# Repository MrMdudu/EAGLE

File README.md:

# EAGLE

Eagle files of a SSTC (Solid state tesla coil) project

Schematic from http://www.loneoceans.com/labs/sstc2/
Where you can learn a lot about Tesla coils

Board layout made by myself and not yet tested.

Edit: PCBs were assembled and they work as intended :)

This is my first try at PCD design and there are certainly a lot of flaws

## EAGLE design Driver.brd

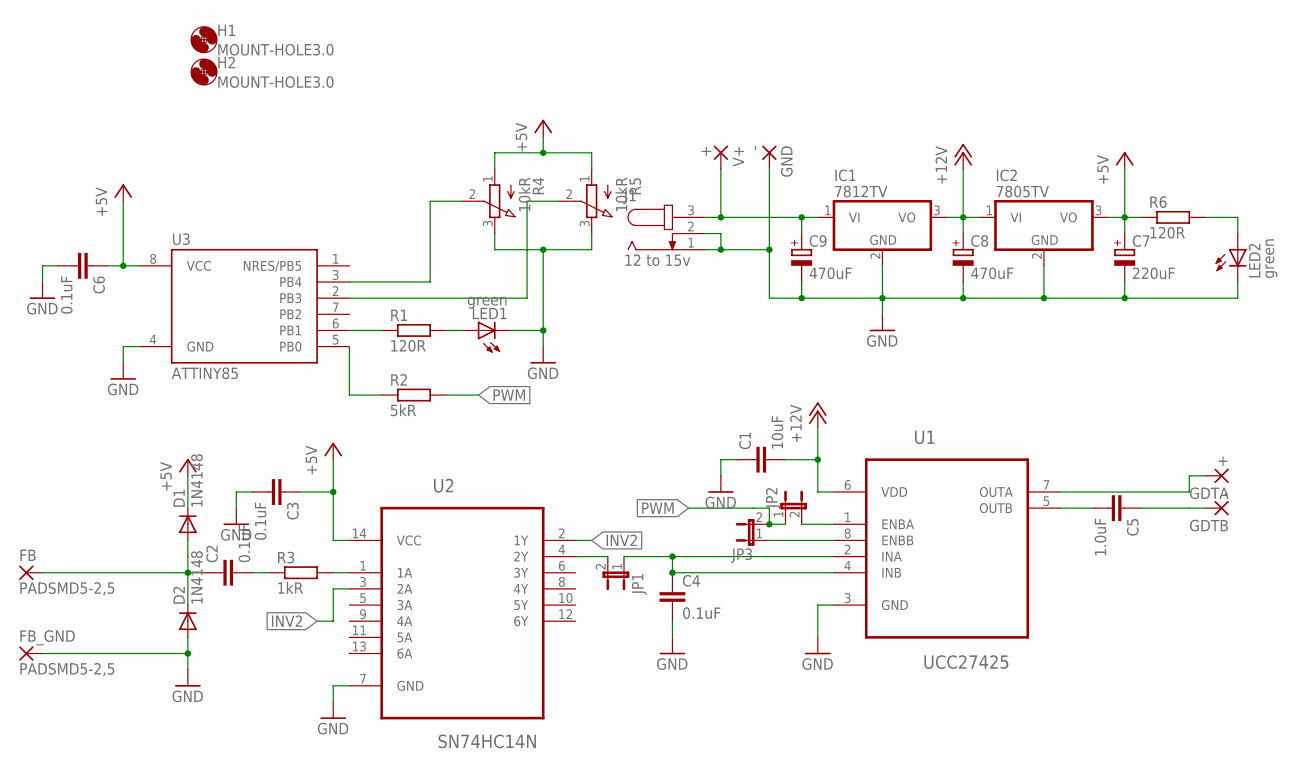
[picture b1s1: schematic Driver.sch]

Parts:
C1: 10uF; 1210
C2, C3, C4, C6: 0.1uF; C0805
C5: 1.0uF; 0805
C7: 220uF; E3,5-8
C8, C9: 470uF; E3,5-10
D1, D2: 1N4148; DO35-7
FB: PADSMD5-2,5; 5-2,5
FB_GND: PADSMD5-2,5; 5-2,5
GDTA: +; 4,16O1,6
GDTB: -; 4,16O1,6
GND: -; 4,16O1,6
H1, H2: MOUNT-HOLE3.0; 3,0
IC1: 7812TV; TO220V
IC2: 7805TV; TO220V
J1: 12 to 15v; SPC4078
JP1, JP2, JP3: JP1E; JP1
LED1, LED2: green; CHIPLED_0805
R1, R6: 120R; R0805
R2: 5kR; R0805
R3: 1kR; R0805
R4, R5: 10kR; 3RP/1610N
U1: UCC27425; DIP254P762X419-8
U2: SN74HC14N; DIP254P762X508-14
U3: ATTINY85; DIL08
V+: +; 4,16O1,6

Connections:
+5V: C3.1, C6.1, C7.+, D1.C, IC2.3 (VO), R4.1 (A), R5.1 (A), R6.1, U2.14 (VCC), U3.8 (VCC)
+12V: C1.2, C8.+, IC1.3 (VO), IC2.1 (VI), U1.6 (VDD)
GDTA: GDTA.1, U1.7 (OUTA)
GDTB: C5.1, GDTB.1
GND: C1.1, C3.2, C4.2, C6.2, C7.-, C8.-, C9.-, D2.A, FB_GND.1, GND.1, IC1.2 (GND), IC2.2 (GND), J1.1, J1.2, LED1.C, LED2.C, R4.3 (E), R5.3 (E), U1.3 (GND), U2.7 (GND), U3.4 (GND)
INV2: U2.2 (1Y), U2.3 (2A)
unnamed: R3.2, U2.1 (1A)
unnamed: C2.2, R3.1
unnamed: C2.1, D1.A, D2.C, FB.1
unnamed: C4.1, JP1.1, U1.2 (INA), U1.4 (INB)
unnamed: R1.1, U3.6 (PB1)
unnamed: LED1.A, R1.2
unnamed: C5.2, U1.5 (OUTB)
unnamed: R4.2 (S), U3.3 (PB4)
unnamed: R5.2 (S), U3.2 (PB3)
unnamed: R2.1, U3.5 (PB0)
unnamed: LED2.A, R6.2
unnamed: JP2.2, U1.1 (ENBA)
unnamed: C9.+, IC1.1 (VI), J1.3, V+.1
unnamed: JP1.2, U2.4 (2Y)
unnamed: JP3.1, U1.8 (ENBB)
PWM: JP2.1, JP3.2, R2.2

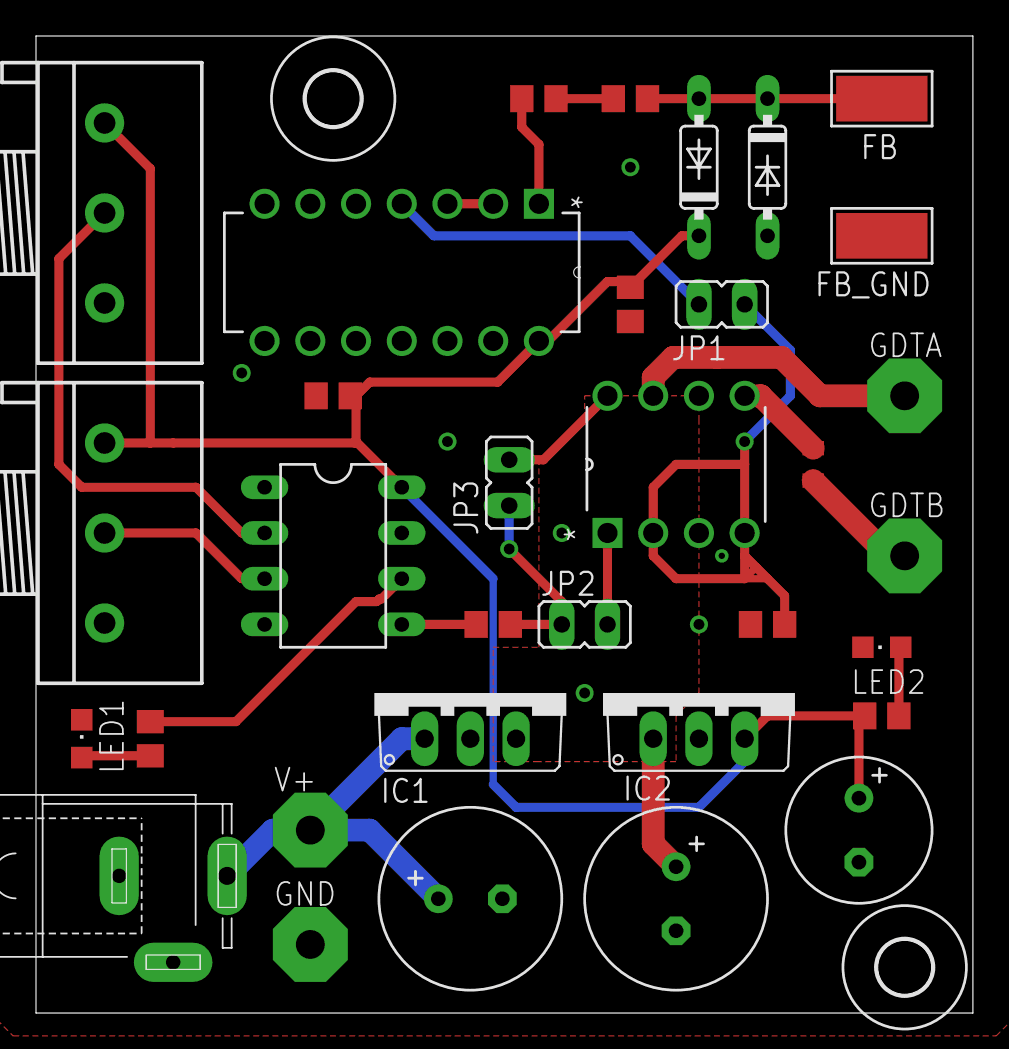
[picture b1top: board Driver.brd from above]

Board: 2 copper layers, 52.0 x 54.3 mm, 36 parts (1 on the bottom side), 22 nets.

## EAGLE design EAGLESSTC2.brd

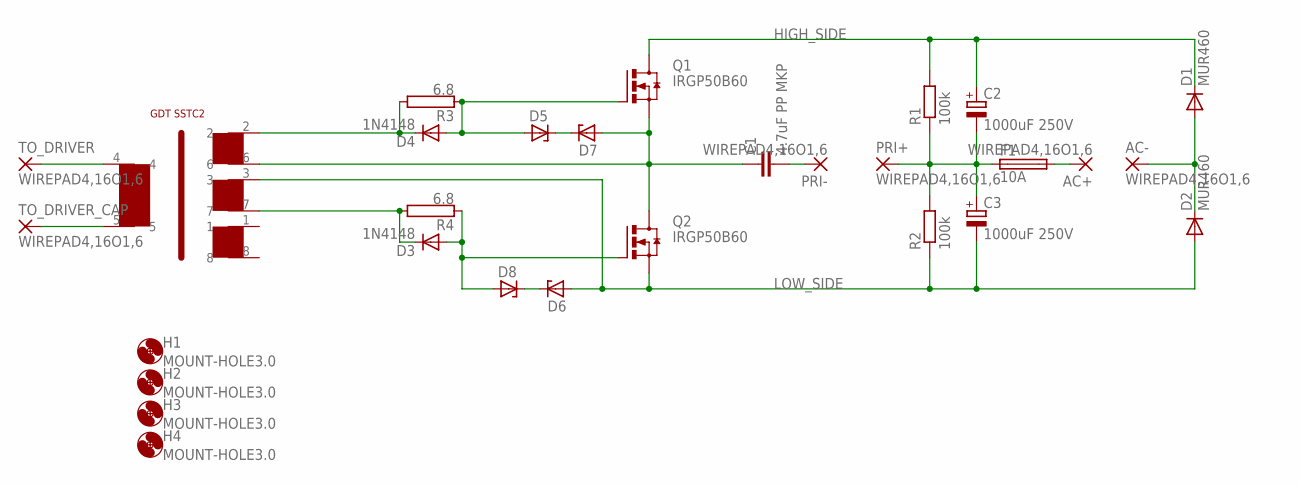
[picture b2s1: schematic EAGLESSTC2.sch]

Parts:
AC+: WIREPAD4,16O1,6; 4,16O1,6
AC-: WIREPAD4,16O1,6; 4,16O1,6
C1: 4.7uF PP MKP; C37.5B20
C2, C3: 1000uF 250V; EB35D
D1, D2: MUR460; C2673
D3, D4: 1N4148; DO35-10
D5, D6, D7, D8: ZENER-DIODEZD-10; ZDIO-10
F1: 10A; SH22
H1, H2, H3, H4: MOUNT-HOLE3.0; 3,0
PRI+: WIREPAD4,16O1,6; 4,16O1,6
PRI-: WIREPAD4,16O1,6; 4,16O1,6
Q1, Q2: IRGP50B60; TO-247AD-V
R1, R2: 100k; 0207/10
R3, R4: 6.8; RWM6X22
TO_DRIVER: WIREPAD4,16O1,6; 4,16O1,6
TO_DRIVER_CAP: WIREPAD4,16O1,6; 4,16O1,6
U$1: ATX-TRANSFORMER_01

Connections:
CAP_TO_GDT: TO_DRIVER_CAP.1, U$1.5
DRIVER_PIN7: TO_DRIVER.1, U$1.4
HIGH_SIDE: C2.+, D1.C, Q1.D, R1.2
LOW_SIDE: C3.-, D2.A, D6.A, Q2.S, R2.1, U$1.3
unnamed: C1.1, D7.A, Q1.S, Q2.D, U$1.6
unnamed: C1.2, PRI-.1
unnamed: AC+.1, F1.2
unnamed: D6.C, D8.C
unnamed: D5.C, D7.C
unnamed: AC-.1, D1.A, D2.C
unnamed: D3.C, R4.2, U$1.7
unnamed: C2.-, C3.+, F1.1, PRI+.1, R1.1, R2.2
unnamed: D4.C, R3.2, U$1.2
unnamed: D4.A, D5.A, Q1.G, R3.1
unnamed: D3.A, D8.A, Q2.G, R4.1

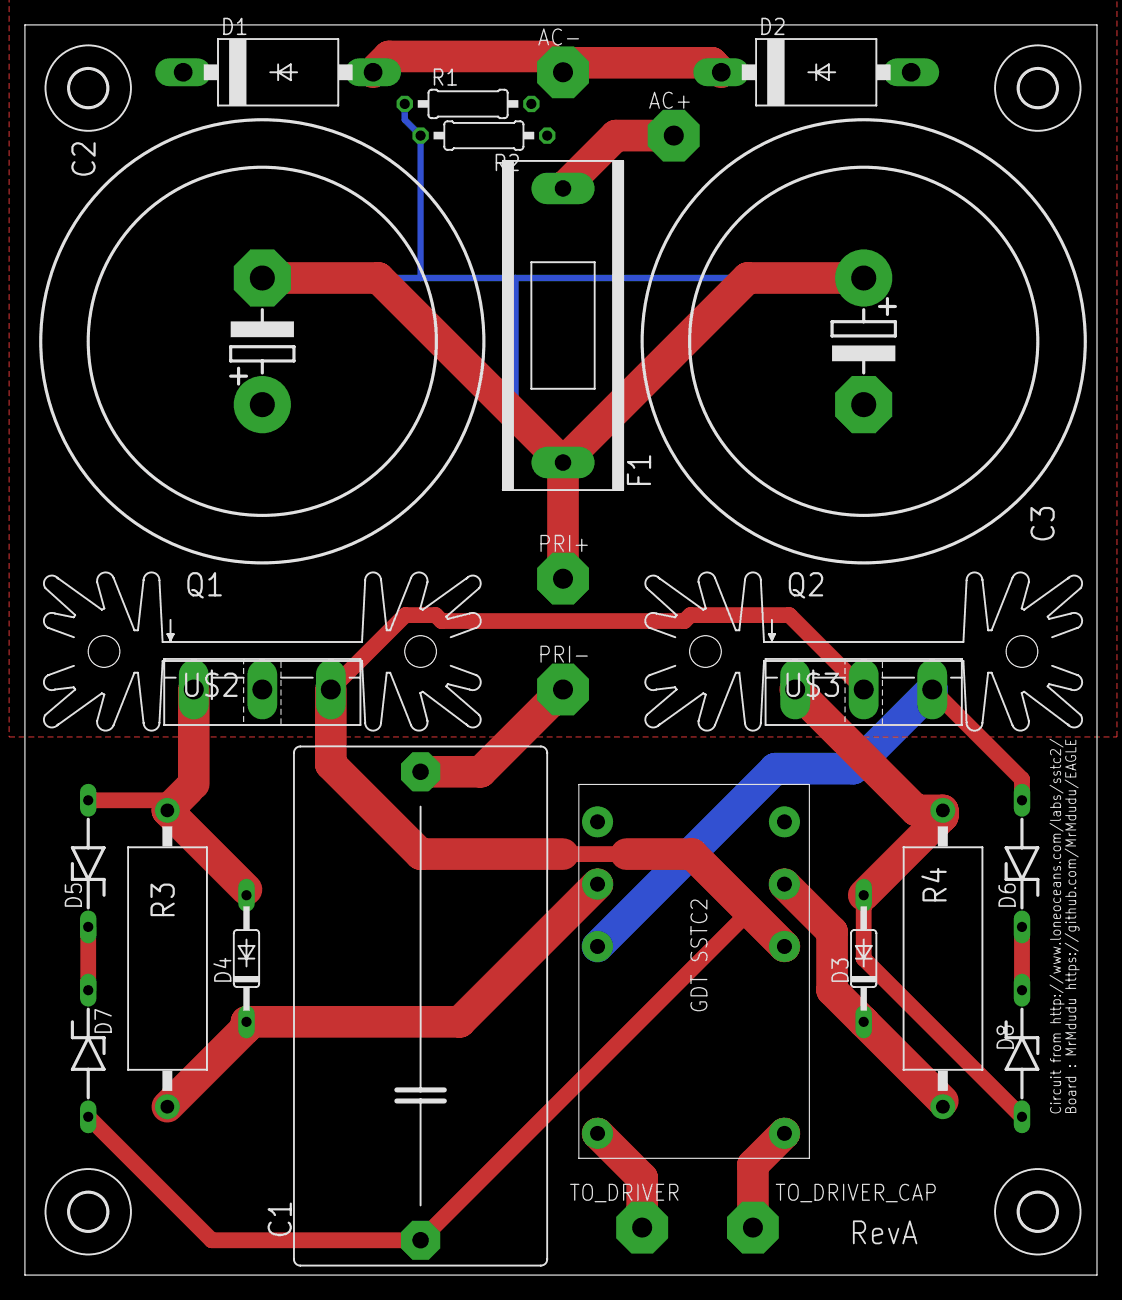
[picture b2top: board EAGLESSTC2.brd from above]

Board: 2 copper layers, 86.0 x 100.3 mm, 31 parts (0 on the bottom side), 15 nets.

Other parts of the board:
U$2, U$3: SK104

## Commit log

2018-09-13 Half bridge circuit and board
2018-09-13 Driver circuit and layout

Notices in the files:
parts and their libraries:
SparkFun-Capacitors: Licensing: Creative Commons ShareAlike 4.0 International - https://creativecommons.org/licenses/by-sa/4.0
